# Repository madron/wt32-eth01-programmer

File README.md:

https://github.com/snakeye/ch340g-esp32
https://en.ovcharov.me/2019/08/16/ch340g-programmer-for-esp8266-esp32/

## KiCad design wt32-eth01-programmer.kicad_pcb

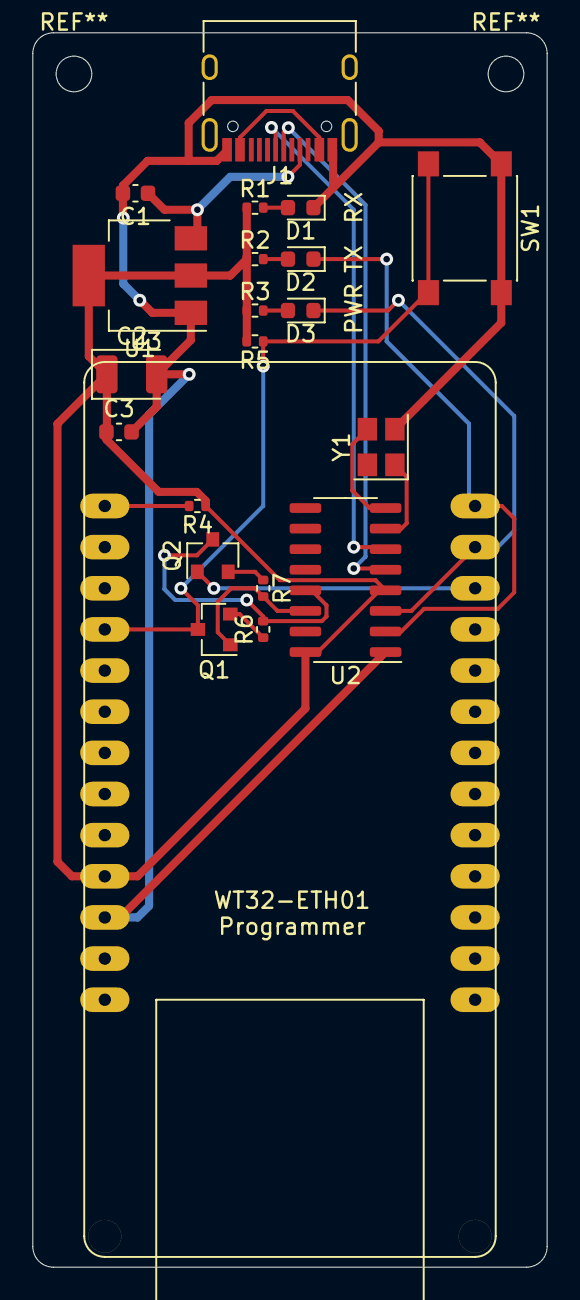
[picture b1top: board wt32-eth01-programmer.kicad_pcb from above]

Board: 2 copper layers, 31.8 x 76.2 mm, 21 parts (0 on the bottom side), 20 nets.

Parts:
C1, C3: 10uF; C_0603_1608Metric
C2: 100uF; CP_EIA-3528-21_Kemet-B
D1, D2, D3: LED; LED_0603_1608Metric
J1: USB_C_Receptacle_USB2.0; USB_C_Receptacle_HRO_TYPE-C-31-M-12
Q1, Q2: S8050; SOT-23
R1, R2, R3: 470; R_0402_1005Metric
R4, R5, R6, R7: 10k; R_0402_1005Metric
SW1: SW_DPST_x2; SW_Push_1P1T_NO_6x6mm_H9.5mm
U1: AMS1117-3.3; SOT-223-3_TabPin2
U2: CH340G; SOIC-16_3.9x9.9mm_P1.27mm
U3: WT32-ETH0-Board
Y1: 12Mhz; Crystal_SMD_3225-4Pin_3.2x2.5mm

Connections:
+3V3: C2.1, C3.1, R1.1, R2.1, R3.1, R4.1, R5.2, U1.2, U2.4, U2.16, U3.10
+5V: C1.1, J1.A5, U1.3
CHPD: R4.2, U3.1
D+: J1.A6, U2.5
D-: J1.A7, U2.6
DTR: Q2.3, R6.2, U2.13
GND: C1.2, C2.2, C3.2, D1.1, J1.A1, J1.A12, J1.B1, J1.B12, SW1.1, U1.1, U2.1, U3.11, Y1.2
I00: Q2.1, U3.24
unnamed: D1.2, R1.2
unnamed: D2.2, R2.2
unnamed: D3.2, R3.2
unnamed: J1.A4, J1.A9, J1.B4, J1.B9
unnamed: Q1.2, R6.1
unnamed: Q2.2, R7.1
unnamed: U2.7, Y1.1
unnamed: U2.8, Y1.3
RST: Q1.3, R5.1, SW1.2, U3.4
RTS: Q1.1, R7.2, U2.14
RX: D3.1, U2.3, U3.25
TX: D2.1, U2.2, U3.26

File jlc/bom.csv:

10uF Unpolarized capacitor,"C1,C3",C_0603_1608Metric,C19702
100uF Polarized capacitor,C2,CP_EIA-3528-21_Kemet-B,C16133
LED Light emitting diode,"D1,D2,D3",LED_0603_1608Metric,C2286
USB_C_Receptacle_USB2.0 USB 2.0-only Type-C Receptacle connector,J1,USB_C_Receptacle_HRO_TYPE-C-31-M-12,C165948
"S8050 0.7A Ic, 20V Vce, Low Voltage High Current NPN Transistor, TO-92","Q1,Q2",SOT-23,C2146
470 Resistor,"R1,R2,R3",R_0402_1005Metric,C25117
10k Resistor,"R4,R5,R6,R7",R_0402_1005Metric,C25744
"SW_DPST_x2 Single Pole Single Throw (SPST) switch, separate symbol",SW1,SW_Push_1P1T_NO_6x6mm_H9.5mm,C127509
"AMS1117-3.3 1A Low Dropout regulator, positive, 3.3V fixed output, SOT-223",U1,SOT-223-3_TabPin2,C6186
"CH340G USB serial converter, UART, SOIC-16",U2,SOIC-16_3.9x9.9mm_P1.27mm,C14267
12Mhz Three pin ceramic resonator,Y1,Crystal_SMD_3225-4Pin_3.2x2.5mm,C9002

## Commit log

2021-05-16 empty project
2021-05-16 add doc
2021-05-16 add readme
2021-05-16 add usb and micro sheets
2021-05-16 add wt32-eth0 to micro sheet
2021-05-16 add pcb draft
2021-05-27 Update transistor
2021-05-27 remove micro sheet
2021-05-27 remove usb sheet
2021-05-27 annotations
2021-05-27 pcb layout draft
2021-05-27 layout
2021-05-27 routing
2021-05-28 add fabrication files
2021-05-29 rename rotattion override
2021-05-29 refactor fab files
2021-05-29 update fab files
2021-06-02 enlarge pads
2021-06-02 rearrange tracks
2021-06-06 fix placement
